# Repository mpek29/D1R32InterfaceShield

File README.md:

# D1R32InterfaceShield 
# 🔌 Modular JST Shield for UNO D1 R32  

## 🚀 Overview  

**D1R32InterfaceShield** is an open-source PCB that provides a reliable, modular interface between the **UNO D1 R32 Board Module** and various external modules via **JST-SM & JST-SH connectors**. It simplifies integration for IoT, automation, and embedded applications.  

## 🎯 Purpose  

- 🔌 **Modular Interface**: Bridges the UNO D1 R32 with sensors, actuators, and peripherals.  
- 📏 **Compact Design**: Optimized layout for small enclosures and prototypes.  
- 🛠️ **Open-source Hardware**: Fully customizable to match your project requirements.  

## 📝 Features  

| 🏷️ Feature                | 🔍 Description                                                 |
|---------------------------|---------------------------------------------------------------|
| 🔌 **Board Compatibility** | Fits the UNO D1 R32 Board Module                              |
| 📡 **Connectors**          | JST-SM & JST-SH for quick, secure connections                 |
| ⚡ **Power Handling**       | Supports 3.3V and 5V logic                                    |
| 🛠️ **GPIO Access**        | Breaks out key digital and analog pins for peripherals         |
| 🔧 **Stability Components**| Includes capacitors for signal conditioning                   |
| 🖥️ **PCB Design**         | Open-source and easy to modify                                 |
| 🌍 **Use Cases**           | IoT, automation, robotics, prototyping                         |

## 📐 PCB Design Preview  
| 📜 Schematic | 🖥️ PCB Layout | 🏗️ 3D |
|--------------|---------------|-------|
|  |  |  |

## 🌟 License  

This project is open-source. Use, modify, and contribute freely. 🚀

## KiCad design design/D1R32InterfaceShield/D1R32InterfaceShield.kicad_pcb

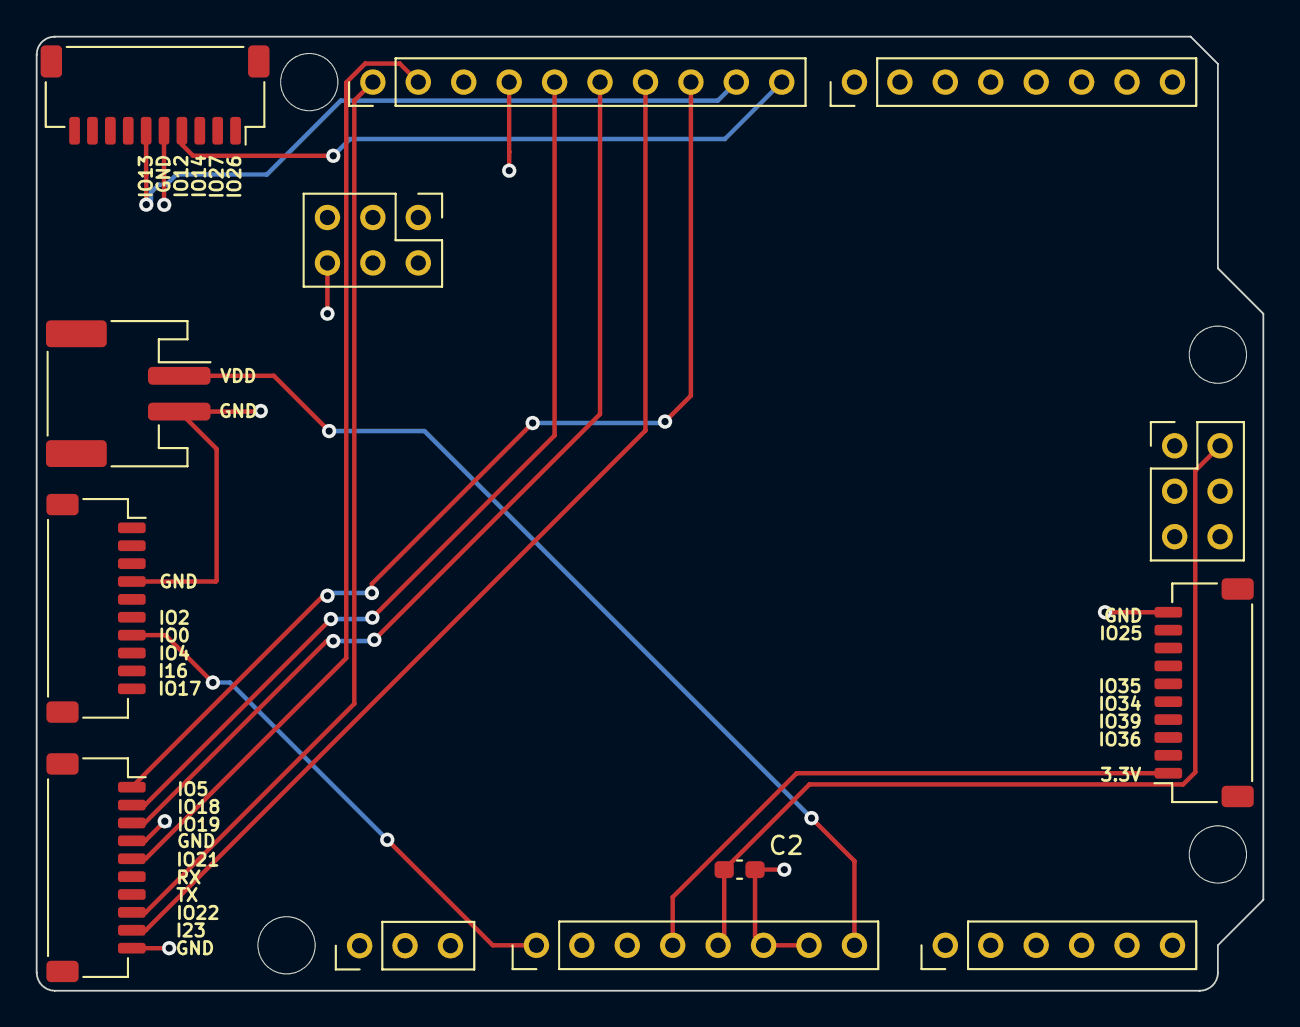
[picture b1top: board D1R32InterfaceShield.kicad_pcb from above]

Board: 2 copper layers, 68.6 x 53.3 mm, 17 parts (0 on the bottom side), 13 nets.

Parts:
C2: 100nF; C_0603_1608Metric_Pad1.08x0.95mm_HandSolder
H1: MountingHole1; Arduino_MountingHole
H2: MountingHole2; Arduino_MountingHole
H3: MountingHole3; Arduino_MountingHole
H4: MountingHole4; Arduino_MountingHole
J4, J5, J6, J7: Conn_01x10; JST_SH_SM10B-SRSS-TB_1x10-1MP_P1.00mm_Horizontal
U2: Analog_1; Arduino_PinSocket_1x08_P2.54mm_Vertical
U3: Analog_2; Arduino_PinSocket_1x06_P2.54mm_Vertical
U4: ESP32-S3; Arduino_PinSocket_2x03_P2.54mm_Vertical
U5: ICSP; Arduino_PinSocket_2x03_P2.54mm_Vertical
U6: Digital_1; Arduino_PinSocket_1x10_P2.54mm_Vertical
U7: Digital_2; Arduino_PinSocket_1x08_P2.54mm_Vertical
U8: Arduino_Header_OFF; Arduino_PinSocket_1x03_P2.54mm_Vertical
VDD: Conn_01x02; JST_PH_S2B-PH-SM4-TB_1x02-1MP_P2.00mm_Horizontal

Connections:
+3.3V: J4.1, U2.4 (+3V3)
+5V: C2.1, U2.5 (+5V), U5.2 (+5V)
GND: C2.2, J4.10, J5.5, J6.1, J6.7, J7.7, U2.6 (GND), U2.7 (GND), U4.6 (GND), U5.6 (GND), U6.4 (GND), U8.2 (GND), VDD.2
IO0: J7.4, U2.1 (BOOT)
IO5: J6.10, U6.8 (~D10/CS/CANTX0)
IO12: J5.4, U6.10 (D8)
IO13: J5.6, U6.9 (~D9)
IO18: J6.9, U6.5 (D13/SCK/CANRX0)
IO19: J6.8, U6.6 (D12/CIPO)
IO21: J6.6, U6.2 (SDA)
IO22: J6.3, U6.1 (SCL)
IO23: J6.2, U6.7 (~D11/COPI)
VDD: U2.8 (VIN), VDD.1

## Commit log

2025-11-05 final version
